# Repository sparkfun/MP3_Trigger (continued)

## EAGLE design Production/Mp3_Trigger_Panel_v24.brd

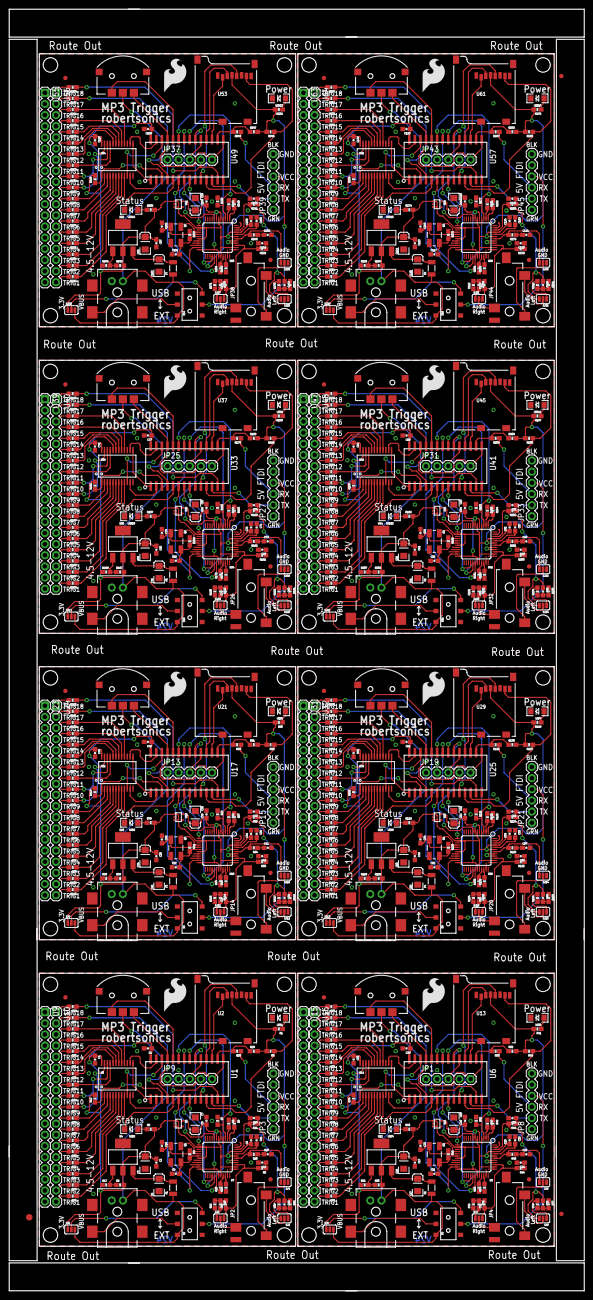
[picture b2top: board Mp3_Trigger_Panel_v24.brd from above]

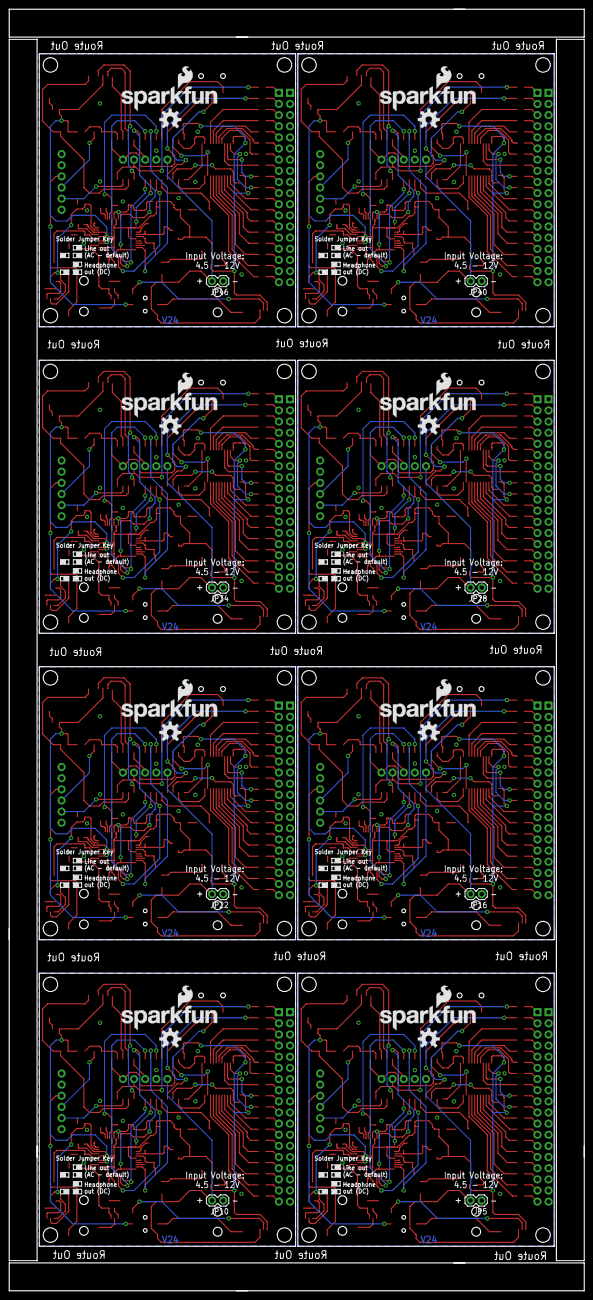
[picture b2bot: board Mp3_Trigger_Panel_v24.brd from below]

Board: 2 copper layers, 131.1 x 292.1 mm, 699 parts (24 on the bottom side), 728 nets.

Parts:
C1, C2, C4, C6, C8, C11, C17, C20, C23, C28, C29, C30, C33, C36, C39, C44, C45, C46, C49, C52, C55, C60, C61, C62, C65, C68, C71, C76, C77, C78, C81, C84, C87, C92, C93, C94, C97, C100, C103, C108, C109, C110, C113, C116, C119, C124, C125, C126: 0.1uF; 0603-CAP
C3, C5, C7, C18, C19, C27, C34, C35, C43, C50, C51, C59, C66, C67, C75, C82, C83, C91, C98, C99, C107, C114, C115, C123: 10uF; EIA3216
C9, C10, C21, C22, C37, C38, C53, C54, C69, C70, C85, C86, C101, C102, C117, C118: 22pF; 0603-CAP
C12, C14, C24, C26, C40, C42, C56, C58, C72, C74, C88, C90, C104, C106, C120, C122: 10nF; 0603-CAP
C13, C25, C41, C57, C73, C89, C105, C121: 47nF; 0603-CAP
C15, C16, C31, C32, C47, C48, C63, C64, C79, C80, C95, C96, C111, C112, C127, C128: 10uF; 0603-CAP
E$1: FIDUCIAL-1.5X3
E$5, E$6: FIDUCIAL-1X2
F1, F2, F3, F4, F5, F6, F7, F8: PTC; PTC-1206
J1, J2, J3, J4, J5, J6, J7, J8: POWER_JACKTOE; POWER_JACK_SMD_OVERPASTE_TOE
JP1, JP9, JP13, JP19, JP25, JP31, JP37, JP43: ISSP; 1X05
JP2, JP4, JP14, JP20, JP26, JP32, JP38, JP44: AUDIO-JACK; AUDIO-JACK-3.5MM-SMD
JP3, JP8, JP15, JP21, JP27, JP33, JP39, JP45: FTDI Basic; 1X06
JP5, JP10, JP16, JP22, JP28, JP34, JP40, JP46: TestPoints; 1X02
JP6, JP7, JP11, JP12, JP17, JP18, JP23, JP24, JP29, JP30, JP35, JP36, JP41, JP42, JP47, JP48: FIDUCIAL1X2; FIDUCIAL-1X2
LED1, LED3, LED5, LED7, LED9, LED11, LED13, LED15: RED; LED-1206
LED2, LED4, LED6, LED8, LED10, LED12, LED14, LED16: GREEN; LED-1206
LOGO1, LOGO2, LOGO5, LOGO7, LOGO9, LOGO11, LOGO13, LOGO15: SFE_LOGO_FLAME.3_INCH; SFE_LOGO_FLAME_.3
LOGO3, LOGO4, LOGO6, LOGO8, LOGO10, LOGO12, LOGO14, LOGO16: OSHW-LOGOM; OSHW-LOGO-M
Q1, Q2, Q3, Q4, Q5, Q6, Q7, Q8: 12.288MHz; CRYSTAL-SMD-5X3
R1, R12, R41, R74, R80, R113, R119, R152, R158, R191, R197, R230, R236, R269, R275, R308: 1K; 0603-RES
R2, R40, R79, R118, R157, R196, R235, R274: 330; 0603-RES
R3, R42, R81, R120, R159, R198, R237, R276: 1M; 0603-RES
R4, R7, R8, R14, R15, R43, R47, R48, R54, R55, R82, R86, R87, R93, R94, R121, R125, R126, R132, R133, R160, R164, R165, R171, R172, R199, R203, R204, R210, R211, R238, R242, R243, R249, R250, R277, R281, R282, R288, R289: 100k; 0603-RES
R5, R49, R88, R127, R166, R205, R244, R283: 47K; 0603-RES
R6, R50, R89, R128, R167, R206, R245, R284: 240; 0603-RES
R9, R10, R11, R44, R45, R46, R83, R84, R85, R122, R123, R124, R161, R162, R163, R200, R201, R202, R239, R240, R241, R278, R279, R280: 20; 0603-RES
R13, R39, R75, R78, R114, R117, R153, R156, R192, R195, R231, R234, R270, R273, R309, R312: 100/.25W; 0603-RES
R16, R18, R19, R52, R76, R77, R91, R115, R116, R130, R154, R155, R169, R193, R194, R208, R232, R233, R247, R271, R272, R286, R310, R311: 10K; 0603-RES
R17, R51, R90, R129, R168, R207, R246, R285: 390; 0603-RES
R20, R21, R22, R23, R24, R25, R26, R27, R28, R29, R30, R31, R32, R33, R34, R35, R36, R37, R38, R53, R56, R57, R58, R59, R60, R61, R62, R63, R64, R65, R66, R67, R68, R69, R70, R71, R72, R73, R92, R95, R96, R97, R98, R99, R100, R101, R102, R103, R104, R105, R106, R107, R108, R109, R110, R111, R112, R131, R134, R135, R136, R137, R138, R139, R140, R141, R142, R143, R144, R145, R146, R147, R148, R149, R150, R151, R170, R173, R174, R175, R176, R177, R178, R179, R180, R181, R182, R183, R184, R185, R186, R187, R188, R189, R190, R209, R212, R213, R214, R215, R216, R217, R218, R219, R220, R221, R222, R223, R224, R225, R226, R227, R228, R229, R248, R251, R252, R253, R254, R255, R256, R257, R258, R259, R260, R261, R262, R263, R264, R265, R266, R267, R268, R287, R290, R291, R292, R293, R294, R295, R296, R297, R298, R299, R300, R301, R302, R303, R304, R305, R306, R307: 100; 0603-RES
S1, S3, S5, S7, S9, S11, S13, S15: NAV_SWITCHSMD; NAV_SWITCH
S2, S4, S6, S8, S10, S12, S14, S16: DPDT; AYZ0202
SJ1, SJ5, SJ9, SJ13, SJ17, SJ21, SJ25, SJ29: UART Power; PAD-JUMPER-3-2OF3_NC_BY_PASTE_YES_SILK_FULL_BOX
SJ2, SJ8, SJ12, SJ16, SJ20, SJ24, SJ28, SJ32: AudioLeft; PAD-HUMPER-3-1&2_NC_BY_PASTE_YES_SILK_FULL_BOX
SJ3, SJ7, SJ11, SJ15, SJ19, SJ23, SJ27, SJ31: AudioRight; PAD-HUMPER-3-1&2_NC_BY_PASTE_YES_SILK_FULL_BOX
SJ4, SJ6, SJ10, SJ14, SJ18, SJ22, SJ26, SJ30: AudioGND; PAD-HUMPER-3-1&2_NC_BY_PASTE_YES_SILK_FULL_BOX
U1, U6, U17, U25, U33, U41, U49, U57: CY8C29466; SOIC-28
U2, U13, U21, U29, U37, U45, U53, U61: USD-SOCKET; MICROSD_1:1
U3, U14, U22, U30, U38, U46, U54, U62: MUX-74HC4067SMD; SSOP24
U4, U12, U20, U28, U36, U44, U52, U60: LM1117; SOT223
U5, U11, U19, U27, U35, U43, U51, U59: 1.8V Reg; SC70
U7, U8, U18, U26, U34, U42, U50, U58: VS1063; LQFP-48
U9, U10, U15, U16, U23, U24, U31, U32, U39, U40, U47, U48, U55, U56, U63, U64: M18_; 1X18
U$1, U$2, U$7, U$16, U$21, U$26, U$31, U$36: SFE_LOGO_NAME_FLAME.2_INCH; SFE_LOGO_NAME_FLAME_.2
U$3, U$4, U$5, U$6, U$8, U$9, U$10, U$11, U$12, U$13, U$14, U$15, U$17, U$18, U$19, U$20, U$22, U$23, U$24, U$25, U$27, U$28, U$29, U$30, U$32, U$33, U$34, U$35, U$37, U$38, U$39, U$40: STAND-OFF

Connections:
3.3V: C1.1, C2.1, C3.A, C4.1, C6.1, R1.2, R2.2, R5.2, R6.2, R12.2, R19.2, SJ1.1, U1.28, U2.4, U3.24, U4.2, U5.1, U5.3, U7.6, U7.14, U7.19, U7.32, U7.38, U7.43, U7.45
3.3V1: C17.1, C18.A, C28.1, C29.1, C30.1, R40.2, R41.2, R49.2, R50.2, R52.2, R74.2, SJ5.1, U6.28, U8.6, U8.14, U8.19, U8.32, U8.38, U8.43, U8.45, U11.1, U11.3, U12.2, U13.4, U14.24
3.3V2: C33.1, C34.A, C44.1, C45.1, C46.1, R79.2, R80.2, R88.2, R89.2, R91.2, R113.2, SJ9.1, U17.28, U18.6, U18.14, U18.19, U18.32, U18.38, U18.43, U18.45, U19.1, U19.3, U20.2, U21.4, U22.24
3.3V3: C49.1, C50.A, C60.1, C61.1, C62.1, R118.2, R119.2, R127.2, R128.2, R130.2, R152.2, SJ13.1, U25.28, U26.6, U26.14, U26.19, U26.32, U26.38, U26.43, U26.45, U27.1, U27.3, U28.2, U29.4, U30.24
3.3V4: C65.1, C66.A, C76.1, C77.1, C78.1, R157.2, R158.2, R166.2, R167.2, R169.2, R191.2, SJ17.1, U33.28, U34.6, U34.14, U34.19, U34.32, U34.38, U34.43, U34.45, U35.1, U35.3, U36.2, U37.4, U38.24
3.3V5: C81.1, C82.A, C92.1, C93.1, C94.1, R196.2, R197.2, R205.2, R206.2, R208.2, R230.2, SJ21.1, U41.28, U42.6, U42.14, U42.19, U42.32, U42.38, U42.43, U42.45, U43.1, U43.3, U44.2, U45.4, U46.24
3.3V6: C97.1, C98.A, C108.1, C109.1, C110.1, R235.2, R236.2, R244.2, R245.2, R247.2, R269.2, SJ25.1, U49.28, U50.6, U50.14, U50.19, U50.32, U50.38, U50.43, U50.45, U51.1, U51.3, U52.2, U53.4, U54.24
3.3V7: C113.1, C114.A, C124.1, C125.1, C126.1, R274.2, R275.2, R283.2, R284.2, R286.2, R308.2, SJ29.1, U57.28, U58.6, U58.14, U58.19, U58.32, U58.38, U58.43, U58.45, U59.1, U59.3, U60.2, U61.4, U62.24
COM: R12.1, U1.3, U3.1
COM1: R74.1, U6.3, U14.1
COM2: R113.1, U17.3, U22.1
COM3: R152.1, U25.3, U30.1
COM4: R191.1, U33.3, U38.1
COM5: R230.1, U41.3, U46.1
COM6: R269.1, U49.3, U54.1
COM7: R308.1, U57.3, U62.1
CVDD: C7.A, C8.1, U5.5, U7.5, U7.7, U7.24, U7.31
CVDD1: C19.A, C20.1, U8.5, U8.7, U8.24, U8.31, U11.5
CVDD2: C35.A, C36.1, U18.5, U18.7, U18.24, U18.31, U19.5
CVDD3: C51.A, C52.1, U26.5, U26.7, U26.24, U26.31, U27.5
CVDD4: C67.A, C68.1, U34.5, U34.7, U34.24, U34.31, U35.5
CVDD5: C83.A, C84.1, U42.5, U42.7, U42.24, U42.31, U43.5
CVDD6: C99.A, C100.1, U50.5, U50.7, U50.24, U50.31, U51.5
CVDD7: C115.A, C116.1, U58.5, U58.7, U58.24, U58.31, U59.5
FCS: U1.17, U2.2
FCS1: U6.17, U13.2
FCS2: U17.17, U21.2
FCS3: U25.17, U29.2
FCS4: U33.17, U37.2
FCS5: U41.17, U45.2
FCS6: U49.17, U53.2
FCS7: U57.17, U61.2
FDI: U1.18, U2.3
FDI1: U6.18, U13.3
FDI2: U17.18, U21.3
FDI3: U25.18, U29.3
FDI4: U33.18, U37.3
FDI5: U41.18, U45.3
FDI6: U49.18, U53.3
FDI7: U57.18, U61.3
FDO: R5.1, U1.11, U2.7
FDO1: R49.1, U6.11, U13.7
FDO2: R88.1, U17.11, U21.7
FDO3: R127.1, U25.11, U29.7
FDO4: R166.1, U33.11, U37.7
FDO5: R205.1, U41.11, U45.7
FDO6: R244.1, U49.11, U53.7
FDO7: R283.1, U57.11, U61.7
FSCK: U1.10, U2.5
FSCK1: U6.10, U13.5
FSCK2: U17.10, U21.5
FSCK3: U25.10, U29.5
FSCK4: U33.10, U37.5
FSCK5: U41.10, U45.5
FSCK6: U49.10, U53.5
FSCK7: U57.10, U61.5
GBUF: R10.2, SJ4.3, U7.42
GBUF1: R45.2, SJ6.3, U8.42
GBUF2: R84.2, SJ10.3, U18.42
GBUF3: R123.2, SJ14.3, U26.42
GBUF4: R162.2, SJ18.3, U34.42
GBUF5: R201.2, SJ22.3, U42.42
GBUF6: R240.2, SJ26.3, U50.42
GBUF7: R279.2, SJ30.3, U58.42
GND: C1.2, C2.2, C3.C, C4.2, C5.C, C6.2, C7.C, C8.2, C9.1, C10.1, C11.1, C12.2, C13.2, C14.2, J1.GND, J1.P$4, JP3.6, JP5.1, JP9.2, LED1.C, R4.1, R7.1, R8.1, R14.1, R15.1, R16.1, R17.1, R18.1, S1.C, SJ4.1, U1.14, U2.6, U2.CD1, U2.CD2, U2.GND1, U2.GND3, U3.12, U3.15, U5.2, U7.4, U7.16, U7.20, U7.21, U7.22, U7.35, U7.37, U7.40, U7.41, U7.47, U9.1, U9.2, U9.3, U9.4, U9.5, U9.6, U9.7, U9.8, U9.9, U9.10, U9.11, U9.12, U9.13, U9.14, U9.15, U9.16, U9.17, U9.18
GND1: C17.2, C18.C, C19.C, C20.2, C21.1, C22.1, C23.1, C24.2, C25.2, C26.2, C27.C, C28.2, C29.2, C30.2, J2.GND, J2.P$4, JP1.2, JP8.6, JP10.1, LED3.C, R43.1, R47.1, R48.1, R51.1, R54.1, R55.1, R76.1, R77.1, S3.C, SJ6.1, U6.14, U8.4, U8.16, U8.20, U8.21, U8.22, U8.35, U8.37, U8.40, U8.41, U8.47, U11.2, U13.6, U13.CD1, U13.CD2, U13.GND1, U13.GND3, U14.12, U14.15, U15.1, U15.2, U15.3, U15.4, U15.5, U15.6, U15.7, U15.8, U15.9, U15.10, U15.11, U15.12, U15.13, U15.14, U15.15, U15.16, U15.17, U15.18
GND2: C33.2, C34.C, C35.C, C36.2, C37.1, C38.1, C39.1, C40.2, C41.2, C42.2, C43.C, C44.2, C45.2, C46.2, J3.GND, J3.P$4, JP13.2, JP15.6, JP16.1, LED5.C, R82.1, R86.1, R87.1, R90.1, R93.1, R94.1, R115.1, R116.1, S5.C, SJ10.1, U17.14, U18.4, U18.16, U18.20, U18.21, U18.22, U18.35, U18.37, U18.40, U18.41, U18.47, U19.2, U21.6, U21.CD1, U21.CD2, U21.GND1, U21.GND3, U22.12, U22.15, U23.1, U23.2, U23.3, U23.4, U23.5, U23.6, U23.7, U23.8, U23.9, U23.10, U23.11, U23.12, U23.13, U23.14, U23.15, U23.16, U23.17, U23.18
GND3: C49.2, C50.C, C51.C, C52.2, C53.1, C54.1, C55.1, C56.2, C57.2, C58.2, C59.C, C60.2, C61.2, C62.2, J4.GND, J4.P$4, JP19.2, JP21.6, JP22.1, LED7.C, R121.1, R125.1, R126.1, R129.1, R132.1, R133.1, R154.1, R155.1, S7.C, SJ14.1, U25.14, U26.4, U26.16, U26.20, U26.21, U26.22, U26.35, U26.37, U26.40, U26.41, U26.47, U27.2, U29.6, U29.CD1, U29.CD2, U29.GND1, U29.GND3, U30.12, U30.15, U31.1, U31.2, U31.3, U31.4, U31.5, U31.6, U31.7, U31.8, U31.9, U31.10, U31.11, U31.12, U31.13, U31.14, U31.15, U31.16, U31.17, U31.18
GND4: C65.2, C66.C, C67.C, C68.2, C69.1, C70.1, C71.1, C72.2, C73.2, C74.2, C75.C, C76.2, C77.2, C78.2, J5.GND, J5.P$4, JP25.2, JP27.6, JP28.1, LED9.C, R160.1, R164.1, R165.1, R168.1, R171.1, R172.1, R193.1, R194.1, S9.C, SJ18.1, U33.14, U34.4, U34.16, U34.20, U34.21, U34.22, U34.35, U34.37, U34.40, U34.41, U34.47, U35.2, U37.6, U37.CD1, U37.CD2, U37.GND1, U37.GND3, U38.12, U38.15, U39.1, U39.2, U39.3, U39.4, U39.5, U39.6, U39.7, U39.8, U39.9, U39.10, U39.11, U39.12, U39.13, U39.14, U39.15, U39.16, U39.17, U39.18
GND5: C81.2, C82.C, C83.C, C84.2, C85.1, C86.1, C87.1, C88.2, C89.2, C90.2, C91.C, C92.2, C93.2, C94.2, J6.GND, J6.P$4, JP31.2, JP33.6, JP34.1, LED11.C, R199.1, R203.1, R204.1, R207.1, R210.1, R211.1, R232.1, R233.1, S11.C, SJ22.1, U41.14, U42.4, U42.16, U42.20, U42.21, U42.22, U42.35, U42.37, U42.40, U42.41, U42.47, U43.2, U45.6, U45.CD1, U45.CD2, U45.GND1, U45.GND3, U46.12, U46.15, U47.1, U47.2, U47.3, U47.4, U47.5, U47.6, U47.7, U47.8, U47.9, U47.10, U47.11, U47.12, U47.13, U47.14, U47.15, U47.16, U47.17, U47.18
GND6: C97.2, C98.C, C99.C, C100.2, C101.1, C102.1, C103.1, C104.2, C105.2, C106.2, C107.C, C108.2, C109.2, C110.2, J7.GND, J7.P$4, JP37.2, JP39.6, JP40.1, LED13.C, R238.1, R242.1, R243.1, R246.1, R249.1, R250.1, R271.1, R272.1, S13.C, SJ26.1, U49.14, U50.4, U50.16, U50.20, U50.21, U50.22, U50.35, U50.37, U50.40, U50.41, U50.47, U51.2, U53.6, U53.CD1, U53.CD2, U53.GND1, U53.GND3, U54.12, U54.15, U55.1, U55.2, U55.3, U55.4, U55.5, U55.6, U55.7, U55.8, U55.9, U55.10, U55.11, U55.12, U55.13, U55.14, U55.15, U55.16, U55.17, U55.18
GND7: C113.2, C114.C, C115.C, C116.2, C117.1, C118.1, C119.1, C120.2, C121.2, C122.2, C123.C, C124.2, C125.2, C126.2, J8.GND, J8.P$4, JP43.2, JP45.6, JP46.1, LED15.C, R277.1, R281.1, R282.1, R285.1, R288.1, R289.1, R310.1, R311.1, S15.C, SJ30.1, U57.14, U58.4, U58.16, U58.20, U58.21, U58.22, U58.35, U58.37, U58.40, U58.41, U58.47, U59.2, U61.6, U61.CD1, U61.CD2, U61.GND1, U61.GND3, U62.12, U62.15, U63.1, U63.2, U63.3, U63.4, U63.5, U63.6, U63.7, U63.8, U63.9, U63.10, U63.11, U63.12, U63.13, U63.14, U63.15, U63.16, U63.17, U63.18
LEFT: C16.1, R11.2, SJ2.3, U7.46
LEFT1: C32.1, R46.2, SJ8.3, U8.46
LEFT2: C48.1, R85.2, SJ12.3, U18.46
LEFT3: C64.1, R124.2, SJ16.3, U26.46
LEFT4: C80.1, R163.2, SJ20.3, U34.46
LEFT5: C96.1, R202.2, SJ24.3, U42.46
LEFT6: C112.1, R241.2, SJ28.3, U50.46
LEFT7: C128.1, R280.2, SJ32.3, U58.46
MCS: U1.22, U7.23
MCS1: U6.22, U8.23
MCS2: U17.22, U18.23
MCS3: U25.22, U26.23
MCS4: U33.22, U34.23
MCS5: U41.22, U42.23
MCS6: U49.22, U50.23
MCS7: U57.22, U58.23
MDCS: U1.7, U7.13
MDCS1: U6.7, U8.13
MDCS2: U17.7, U18.13
MDCS3: U25.7, U26.13
MDCS4: U33.7, U34.13
MDCS5: U41.7, U42.13
MDCS6: U49.7, U50.13
MDCS7: U57.7, U58.13
MDREQ: U1.20, U7.8
MDREQ1: U6.20, U8.8
MDREQ2: U17.20, U18.8
MDREQ3: U25.20, U26.8
MDREQ4: U33.20, U34.8
MDREQ5: U41.20, U42.8
MDREQ6: U49.20, U50.8
MDREQ7: U57.20, U58.8
MICN: R4.2, U7.2
MICN1: R47.2, U8.2
MICN2: R86.2, U18.2
MICN3: R125.2, U26.2
MICN4: R164.2, U34.2
MICN5: R203.2, U42.2
MICN6: R242.2, U50.2
MICN7: R281.2, U58.2
MICP: R8.2, U7.1
MICP1: R48.2, U8.1
MICP2: R87.2, U18.1
MICP3: R126.2, U26.1
MICP4: R165.2, U34.1
MICP5: R204.2, U42.1
MICP6: R243.2, U50.1
MICP7: R282.2, U58.1
MRST: R7.2, U1.23, U7.3
MRST1: R43.2, U6.23, U8.3
MRST2: R82.2, U17.23, U18.3
MRST3: R121.2, U25.23, U26.3
MRST4: R160.2, U33.23, U34.3
MRST5: R199.2, U41.23, U42.3
MRST6: R238.2, U49.23, U50.3
MRST7: R277.2, U57.23, U58.3
MSCLK: U1.8, U7.28
MSCLK1: U6.8, U8.28
MSCLK2: U17.8, U18.28
MSCLK3: U25.8, U26.28
MSCLK4: U33.8, U34.28
MSCLK5: U41.8, U42.28
MSCLK6: U49.8, U50.28
MSCLK7: U57.8, U58.28
MSI: U1.21, U7.29
MSI1: U6.21, U8.29
MSI2: U17.21, U18.29
MSI3: U25.21, U26.29
MSI4: U33.21, U34.29
MSI5: U41.21, U42.29
MSI6: U49.21, U50.29
MSI7: U57.21, U58.29
MSO: U1.6, U7.30
MSO1: U6.6, U8.30
MSO2: U17.6, U18.30
MSO3: U25.6, U26.30
MSO4: U33.6, U34.30
MSO5: U41.6, U42.30
MSO6: U49.6, U50.30
MSO7: U57.6, U58.30
unnamed: JP2.SLEEVE, SJ4.2
unnamed: R6.1, R17.2, U4.1
unnamed: C9.2, Q1.3, R3.2, U7.18
unnamed: LED1.A, R1.1
unnamed: C10.2, Q1.1, R3.1, U7.17
unnamed: JP2.RING, SJ3.2
unnamed: R13.2, SJ3.1
unnamed: C15.2, R13.1, R16.2
unnamed: LED2.A, R2.1
unnamed: R14.2, U7.34
unnamed: C11.2, U7.44
unnamed: LED2.C, U1.5
unnamed: J1.VIN0, S2.2
unnamed: C14.1, R11.1
unnamed: C13.1, R10.1
unnamed: C12.1, R9.1
unnamed: R15.2, U7.33
unnamed: C5.A, F1.2, U4.3
unnamed: JP2.TIP, SJ2.2
unnamed: S2.6, SJ1.2
unnamed: LED3.A, R41.1
unnamed: R39.2, SJ2.1
unnamed: C16.2, R18.2, R39.1
unnamed: J2.VIN0, S4.2
unnamed: C21.2, Q2.3, R42.2, U8.18
unnamed: C22.2, Q2.1, R42.1, U8.17
unnamed: C23.2, U8.44
unnamed: C26.1, R46.1
unnamed: C25.1, R45.1
unnamed: C24.1, R44.1
unnamed: LED4.A, R40.1
unnamed: R50.1, R51.2, U12.1
unnamed: LED4.C, U6.5
unnamed: S4.6, SJ5.2
unnamed: R54.2, U8.34
unnamed: R55.2, U8.33
unnamed: C27.A, F2.2, U12.3
unnamed: JP4.SLEEVE, SJ6.2
unnamed: JP4.RING, SJ7.2
unnamed: R75.2, SJ7.1
unnamed: C31.2, R75.1, R76.2
unnamed: JP4.TIP, SJ8.2
unnamed: R78.2, SJ8.1
unnamed: C32.2, R77.2, R78.1
unnamed: LED5.A, R80.1
unnamed: J3.VIN0, S6.2
unnamed: C37.2, Q3.3, R81.2, U18.18
unnamed: C38.2, Q3.1, R81.1, U18.17
unnamed: C39.2, U18.44
unnamed: C42.1, R85.1
unnamed: C41.1, R84.1
unnamed: C40.1, R83.1
unnamed: LED6.A, R79.1
unnamed: R89.1, R90.2, U20.1
unnamed: LED6.C, U17.5
unnamed: S6.6, SJ9.2
unnamed: R93.2, U18.34
unnamed: R94.2, U18.33
unnamed: C43.A, F3.2, U20.3
unnamed: JP14.SLEEVE, SJ10.2
unnamed: JP14.RING, SJ11.2
unnamed: R114.2, SJ11.1
unnamed: C47.2, R114.1, R115.2
unnamed: JP14.TIP, SJ12.2
unnamed: R117.2, SJ12.1
unnamed: C48.2, R116.2, R117.1
unnamed: LED7.A, R119.1
unnamed: J4.VIN0, S8.2
unnamed: C53.2, Q4.3, R120.2, U26.18
unnamed: C54.2, Q4.1, R120.1, U26.17
unnamed: C55.2, U26.44
unnamed: C58.1, R124.1
unnamed: C57.1, R123.1
unnamed: C56.1, R122.1
unnamed: LED8.A, R118.1
unnamed: R128.1, R129.2, U28.1
unnamed: LED8.C, U25.5
unnamed: S8.6, SJ13.2
unnamed: R132.2, U26.34
unnamed: R133.2, U26.33
unnamed: C59.A, F4.2, U28.3
unnamed: JP20.SLEEVE, SJ14.2
unnamed: JP20.RING, SJ15.2
unnamed: R153.2, SJ15.1
unnamed: C63.2, R153.1, R154.2
unnamed: JP20.TIP, SJ16.2
unnamed: R156.2, SJ16.1
unnamed: C64.2, R155.2, R156.1
unnamed: LED9.A, R158.1
unnamed: J5.VIN0, S10.2
unnamed: C69.2, Q5.3, R159.2, U34.18
unnamed: C70.2, Q5.1, R159.1, U34.17
unnamed: C71.2, U34.44
unnamed: C74.1, R163.1
unnamed: C73.1, R162.1
unnamed: C72.1, R161.1
unnamed: LED10.A, R157.1
unnamed: R167.1, R168.2, U36.1
unnamed: LED10.C, U33.5
unnamed: S10.6, SJ17.2
unnamed: R171.2, U34.34
unnamed: R172.2, U34.33
unnamed: C75.A, F5.2, U36.3
unnamed: JP26.SLEEVE, SJ18.2
unnamed: JP26.RING, SJ19.2
unnamed: R192.2, SJ19.1
unnamed: C79.2, R192.1, R193.2
unnamed: JP26.TIP, SJ20.2
unnamed: R195.2, SJ20.1
unnamed: C80.2, R194.2, R195.1
unnamed: LED11.A, R197.1
unnamed: J6.VIN0, S12.2
unnamed: C85.2, Q6.3, R198.2, U42.18
unnamed: C86.2, Q6.1, R198.1, U42.17
unnamed: C87.2, U42.44
unnamed: C90.1, R202.1
unnamed: C89.1, R201.1
unnamed: C88.1, R200.1
unnamed: LED12.A, R196.1
unnamed: R206.1, R207.2, U44.1
unnamed: LED12.C, U41.5
unnamed: S12.6, SJ21.2
unnamed: R210.2, U42.34
unnamed: R211.2, U42.33
unnamed: C91.A, F6.2, U44.3
unnamed: JP32.SLEEVE, SJ22.2
unnamed: JP32.RING, SJ23.2
unnamed: R231.2, SJ23.1
unnamed: C95.2, R231.1, R232.2
unnamed: JP32.TIP, SJ24.2
unnamed: R234.2, SJ24.1
unnamed: C96.2, R233.2, R234.1
unnamed: LED13.A, R236.1
unnamed: J7.VIN0, S14.2
unnamed: C101.2, Q7.3, R237.2, U50.18
unnamed: C102.2, Q7.1, R237.1, U50.17
unnamed: C103.2, U50.44
unnamed: C106.1, R241.1
unnamed: C105.1, R240.1
unnamed: C104.1, R239.1
unnamed: LED14.A, R235.1
unnamed: R245.1, R246.2, U52.1
unnamed: LED14.C, U49.5
unnamed: S14.6, SJ25.2
unnamed: R249.2, U50.34
unnamed: R250.2, U50.33
unnamed: C107.A, F7.2, U52.3
unnamed: JP38.SLEEVE, SJ26.2
unnamed: JP38.RING, SJ27.2
unnamed: R270.2, SJ27.1
unnamed: C111.2, R270.1, R271.2
unnamed: JP38.TIP, SJ28.2
unnamed: R273.2, SJ28.1
unnamed: C112.2, R272.2, R273.1
unnamed: LED15.A, R275.1
unnamed: J8.VIN0, S16.2
unnamed: C117.2, Q8.3, R276.2, U58.18
unnamed: C118.2, Q8.1, R276.1, U58.17
unnamed: C119.2, U58.44
unnamed: C122.1, R280.1
unnamed: C121.1, R279.1
unnamed: C120.1, R278.1
unnamed: LED16.A, R274.1
unnamed: R284.1, R285.2, U60.1
unnamed: LED16.C, U57.5
unnamed: S16.6, SJ29.2
unnamed: R288.2, U58.34
unnamed: R289.2, U58.33
unnamed: C123.A, F8.2, U60.3
unnamed: JP44.SLEEVE, SJ30.2
unnamed: JP44.RING, SJ31.2
unnamed: R309.2, SJ31.1
unnamed: C127.2, R309.1, R310.2
unnamed: JP44.TIP, SJ32.2
unnamed: R312.2, SJ32.1
unnamed: C128.2, R311.2, R312.1
RIGHT: C15.1, R9.2, SJ3.3, U7.39
RIGHT1: C31.1, R44.2, SJ7.3, U8.39
RIGHT2: C47.1, R83.2, SJ11.3, U18.39
RIGHT3: C63.1, R122.2, SJ15.3, U26.39
RIGHT4: C79.1, R161.2, SJ19.3, U34.39
RIGHT5: C95.1, R200.2, SJ23.3, U42.39
RIGHT6: C111.1, R239.2, SJ27.3, U50.39
RIGHT7: C127.1, R278.2, SJ31.3, U58.39
RX: R19.1, R20.2, U1.16
RX1: R52.1, R53.2, U6.16
RX2: R91.1, R92.2, U17.16
RX3: R130.1, R131.2, U25.16
RX4: R169.1, R170.2, U33.16
RX5: R208.1, R209.2, U41.16
RX6: R247.1, R248.2, U49.16
RX7: R286.1, R287.2, U57.16
RX-I: JP3.3, R20.1
RX-I1: JP8.3, R53.1
RX-I2: JP15.3, R92.1
RX-I3: JP21.3, R131.1
RX-I4: JP27.3, R170.1
RX-I5: JP33.3, R209.1
RX-I6: JP39.3, R248.1
RX-I7: JP45.3, R287.1
S0: U1.26, U3.10
S1: U1.2, U3.11
S2: U1.27, U3.14
S3: U1.1, U3.13
S4: U6.26, U14.10
S5: U6.2, U14.11
S6: U6.27, U14.14
S7: U6.1, U14.13
S8: U17.26, U22.10
S9: U17.2, U22.11
S10: U17.27, U22.14
S11: U17.1, U22.13
S12: U25.26, U30.10
S13: U25.2, U30.11
S14: U25.27, U30.14
S15: U25.1, U30.13
S16: U33.26, U38.10
S17: U33.2, U38.11
S18: U33.27, U38.14
S19: U33.1, U38.13
S20: U41.26, U46.10
S21: U41.2, U46.11
S22: U41.27, U46.14
S23: U41.1, U46.13
S24: U49.26, U54.10
S25: U49.2, U54.11
S26: U49.27, U54.14
S27: U49.1, U54.13
S28: U57.26, U62.10
S29: U57.2, U62.11
S30: U57.27, U62.14
S31: U57.1, U62.13
SW1: S1.1, U1.24
SW2: S1.T, U1.4
SW3: S1.2, U1.25
SW4: S3.T, U6.4
SW5: S3.2, U6.25
SW6: S3.1, U6.24
SW7: S5.T, U17.4
SW8: S5.2, U17.25
SW9: S5.1, U17.24
SW10: S7.T, U25.4
SW11: S7.2, U25.25
SW12: S7.1, U25.24
SW13: S9.T, U33.4
SW14: S9.2, U33.25
SW15: S9.1, U33.24
SW16: S11.T, U41.4
SW17: S11.2, U41.25
SW18: S11.1, U41.24
SW19: S13.T, U49.4
SW20: S13.2, U49.25
SW21: S13.1, U49.24
SW22: S15.T, U57.4
SW23: S15.2, U57.25
SW24: S15.1, U57.24
T1: R36.2, U10.18
T2: R35.2, U10.17
T3: R21.2, U10.16
T4: R22.2, U10.15
T5: R23.2, U10.14
T6: R24.2, U10.13
T7: R25.2, U10.12
T8: R26.2, U10.11
T9: R27.2, U10.10
T10: R28.2, U10.9
T11: R29.2, U10.8
T12: R30.2, U10.7
T13: R31.2, U10.6
T14: R32.2, U10.5
T15: R33.2, U10.4
T16: R34.2, U10.3
T17: R37.2, U10.2
T18: R38.2, U10.1
T19: R71.2, U16.18
T20: R70.2, U16.17
T21: R56.2, U16.16
T22: R57.2, U16.15
T23: R58.2, U16.14
T24: R59.2, U16.13
T25: R60.2, U16.12
T26: R61.2, U16.11
T27: R62.2, U16.10
T28: R63.2, U16.9
T29: R64.2, U16.8
T30: R65.2, U16.7
T31: R66.2, U16.6
T32: R67.2, U16.5
T33: R68.2, U16.4
T34: R69.2, U16.3
T35: R72.2, U16.2
T36: R73.2, U16.1
T37: R110.2, U24.18
T38: R109.2, U24.17
T39: R95.2, U24.16
T40: R96.2, U24.15
T41: R97.2, U24.14
T42: R98.2, U24.13
T43: R99.2, U24.12
T44: R100.2, U24.11
T45: R101.2, U24.10
T46: R102.2, U24.9
T47: R103.2, U24.8
T48: R104.2, U24.7
T49: R105.2, U24.6
T50: R106.2, U24.5
T51: R107.2, U24.4
T52: R108.2, U24.3
T53: R111.2, U24.2
T54: R112.2, U24.1
T55: R149.2, U32.18
T56: R148.2, U32.17
T57: R134.2, U32.16
T58: R135.2, U32.15
T59: R136.2, U32.14
T60: R137.2, U32.13
T61: R138.2, U32.12
T62: R139.2, U32.11
T63: R140.2, U32.10
T64: R141.2, U32.9
T65: R142.2, U32.8
T66: R143.2, U32.7
T67: R144.2, U32.6
T68: R145.2, U32.5
T69: R146.2, U32.4
T70: R147.2, U32.3
T71: R150.2, U32.2
T72: R151.2, U32.1
T73: R188.2, U40.18
T74: R187.2, U40.17
T75: R173.2, U40.16
T76: R174.2, U40.15
T77: R175.2, U40.14
T78: R176.2, U40.13
T79: R177.2, U40.12
T80: R178.2, U40.11
T81: R179.2, U40.10
T82: R180.2, U40.9
T83: R181.2, U40.8
T84: R182.2, U40.7
T85: R183.2, U40.6
T86: R184.2, U40.5
T87: R185.2, U40.4
T88: R186.2, U40.3
T89: R189.2, U40.2
T90: R190.2, U40.1
T91: R227.2, U48.18
T92: R226.2, U48.17
T93: R212.2, U48.16
T94: R213.2, U48.15
T95: R214.2, U48.14
T96: R215.2, U48.13
T97: R216.2, U48.12
T98: R217.2, U48.11
T99: R218.2, U48.10
T100: R219.2, U48.9
T101: R220.2, U48.8
T102: R221.2, U48.7
T103: R222.2, U48.6
T104: R223.2, U48.5
T105: R224.2, U48.4
T106: R225.2, U48.3
T107: R228.2, U48.2
T108: R229.2, U48.1
T109: R266.2, U56.18
T110: R265.2, U56.17
T111: R251.2, U56.16
T112: R252.2, U56.15
T113: R253.2, U56.14
T114: R254.2, U56.13
T115: R255.2, U56.12
T116: R256.2, U56.11
T117: R257.2, U56.10
T118: R258.2, U56.9
T119: R259.2, U56.8
T120: R260.2, U56.7
T121: R261.2, U56.6
T122: R262.2, U56.5
T123: R263.2, U56.4
T124: R264.2, U56.3
T125: R267.2, U56.2
T126: R268.2, U56.1
T127: R305.2, U64.18
T128: R304.2, U64.17
T129: R290.2, U64.16
T130: R291.2, U64.15
T131: R292.2, U64.14
T132: R293.2, U64.13
T133: R294.2, U64.12
T134: R295.2, U64.11
T135: R296.2, U64.10
T136: R297.2, U64.9
T137: R298.2, U64.8
T138: R299.2, U64.7
T139: R300.2, U64.6
T140: R301.2, U64.5
T141: R302.2, U64.4
T142: R303.2, U64.3
T143: R306.2, U64.2
T144: R307.2, U64.1
TRIG1: R36.1, U3.9
TRIG2: R35.1, U3.8
TRIG3: R21.1, U3.7
TRIG4: R22.1, U3.6
TRIG5: R23.1, U3.5
TRIG6: R24.1, U3.4
TRIG7: R25.1, U3.3
TRIG8: R26.1, U3.2
TRIG9: R27.1, U3.23
TRIG10: R28.1, U3.22
TRIG11: R29.1, U3.21
TRIG12: R30.1, U3.20
TRIG13: R31.1, U3.19
TRIG14: R32.1, U3.18
TRIG15: R33.1, U3.17
TRIG16: R34.1, U3.16
TRIG17: JP9.5, R37.1, U1.15
TRIG18: JP9.4, R38.1, U1.13
TRIG19: JP1.5, R72.1, U6.15
TRIG20: JP1.4, R73.1, U6.13
TRIG21: R69.1, U14.16
TRIG22: R68.1, U14.17
TRIG23: R67.1, U14.18
TRIG24: R66.1, U14.19
TRIG25: R65.1, U14.20
TRIG26: R64.1, U14.21
TRIG27: R63.1, U14.22
TRIG28: R62.1, U14.23
TRIG29: R61.1, U14.2
TRIG30: R60.1, U14.3
TRIG31: R59.1, U14.4
TRIG32: R58.1, U14.5
TRIG33: R57.1, U14.6
TRIG34: R56.1, U14.7
TRIG35: R70.1, U14.8
TRIG36: R71.1, U14.9
TRIG37: JP13.5, R111.1, U17.15
TRIG38: JP13.4, R112.1, U17.13
TRIG39: R108.1, U22.16
TRIG40: R107.1, U22.17
TRIG41: R106.1, U22.18
TRIG42: R105.1, U22.19
TRIG43: R104.1, U22.20
TRIG44: R103.1, U22.21
TRIG45: R102.1, U22.22
TRIG46: R101.1, U22.23
TRIG47: R100.1, U22.2
TRIG48: R99.1, U22.3
TRIG49: R98.1, U22.4
TRIG50: R97.1, U22.5
TRIG51: R96.1, U22.6
TRIG52: R95.1, U22.7
TRIG53: R109.1, U22.8
TRIG54: R110.1, U22.9
TRIG55: JP19.5, R150.1, U25.15
TRIG56: JP19.4, R151.1, U25.13
TRIG57: R147.1, U30.16
TRIG58: R146.1, U30.17
TRIG59: R145.1, U30.18
TRIG60: R144.1, U30.19
TRIG61: R143.1, U30.20
TRIG62: R142.1, U30.21
TRIG63: R141.1, U30.22
TRIG64: R140.1, U30.23
TRIG65: R139.1, U30.2
TRIG66: R138.1, U30.3
TRIG67: R137.1, U30.4
TRIG68: R136.1, U30.5
TRIG69: R135.1, U30.6
TRIG70: R134.1, U30.7
TRIG71: R148.1, U30.8
TRIG72: R149.1, U30.9
TRIG73: JP25.5, R189.1, U33.15
TRIG74: JP25.4, R190.1, U33.13
TRIG75: R186.1, U38.16
TRIG76: R185.1, U38.17
TRIG77: R184.1, U38.18
TRIG78: R183.1, U38.19
TRIG79: R182.1, U38.20
TRIG80: R181.1, U38.21
TRIG81: R180.1, U38.22
TRIG82: R179.1, U38.23
TRIG83: R178.1, U38.2
TRIG84: R177.1, U38.3
TRIG85: R176.1, U38.4
TRIG86: R175.1, U38.5
TRIG87: R174.1, U38.6
TRIG88: R173.1, U38.7
TRIG89: R187.1, U38.8
TRIG90: R188.1, U38.9
TRIG91: JP31.5, R228.1, U41.15
TRIG92: JP31.4, R229.1, U41.13
TRIG93: R225.1, U46.16
TRIG94: R224.1, U46.17
TRIG95: R223.1, U46.18
TRIG96: R222.1, U46.19
TRIG97: R221.1, U46.20
TRIG98: R220.1, U46.21
TRIG99: R219.1, U46.22
TRIG100: R218.1, U46.23
TRIG101: R217.1, U46.2
TRIG102: R216.1, U46.3
TRIG103: R215.1, U46.4
TRIG104: R214.1, U46.5
TRIG105: R213.1, U46.6
TRIG106: R212.1, U46.7
TRIG107: R226.1, U46.8
TRIG108: R227.1, U46.9
TRIG109: JP37.5, R267.1, U49.15
TRIG110: JP37.4, R268.1, U49.13
TRIG111: R264.1, U54.16
TRIG112: R263.1, U54.17
TRIG113: R262.1, U54.18
TRIG114: R261.1, U54.19
TRIG115: R260.1, U54.20
TRIG116: R259.1, U54.21
TRIG117: R258.1, U54.22
TRIG118: R257.1, U54.23
TRIG119: R256.1, U54.2
TRIG120: R255.1, U54.3
TRIG121: R254.1, U54.4
TRIG122: R253.1, U54.5
TRIG123: R252.1, U54.6
TRIG124: R251.1, U54.7
TRIG125: R265.1, U54.8
TRIG126: R266.1, U54.9
TRIG127: JP43.5, R306.1, U57.15
TRIG128: JP43.4, R307.1, U57.13
TRIG129: R303.1, U62.16
TRIG130: R302.1, U62.17
TRIG131: R301.1, U62.18
TRIG132: R300.1, U62.19
TRIG133: R299.1, U62.20
TRIG134: R298.1, U62.21
TRIG135: R297.1, U62.22
TRIG136: R296.1, U62.23
TRIG137: R295.1, U62.2
TRIG138: R294.1, U62.3
TRIG139: R293.1, U62.4
TRIG140: R292.1, U62.5
TRIG141: R291.1, U62.6
TRIG142: R290.1, U62.7
TRIG143: R304.1, U62.8
TRIG144: R305.1, U62.9
TX: JP3.2, U1.12
TX1: JP8.2, U6.12
TX2: JP15.2, U17.12
TX3: JP21.2, U25.12
TX4: JP27.2, U33.12
TX5: JP33.2, U41.12
TX6: JP39.2, U49.12
TX7: JP45.2, U57.12
USBVCC: JP3.4, S2.5
USBVCC1: JP8.4, S4.5
USBVCC2: JP15.4, S6.5
USBVCC3: JP21.4, S8.5
USBVCC4: JP27.4, S10.5
USBVCC5: JP33.4, S12.5
USBVCC6: JP39.4, S14.5
USBVCC7: JP45.4, S16.5
VBUS: F1.1, JP5.2, JP9.1, S2.1, SJ1.3
VBUS1: F2.1, JP1.1, JP10.2, S4.1, SJ5.3
VBUS2: F3.1, JP13.1, JP16.2, S6.1, SJ9.3
VBUS3: F4.1, JP19.1, JP22.2, S8.1, SJ13.3
VBUS4: F5.1, JP25.1, JP28.2, S10.1, SJ17.3
VBUS5: F6.1, JP31.1, JP34.2, S12.1, SJ21.3
VBUS6: F7.1, JP37.1, JP40.2, S14.1, SJ25.3
VBUS7: F8.1, JP43.1, JP46.2, S16.1, SJ29.3
XRES: JP9.3, U1.19
XRES1: JP1.3, U6.19
XRES2: JP13.3, U17.19
XRES3: JP19.3, U25.19
XRES4: JP25.3, U33.19
XRES5: JP31.3, U41.19
XRES6: JP37.3, U49.19
XRES7: JP43.3, U57.19

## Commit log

2015-03-10 Adding hardware files, updating README
2015-03-10 Fixing README license
2015-03-10 Adding collaboration info to README
2015-07-09 V24 preliminary rerouting finished
    New V24 preliminary rerouting finished after adding pulp and jumpers on
    audio lines.
2015-07-13 Minor changes from Toni K review
    Acid trap elimination, angles, added notes about jumpers, minor
    rerouting.
2015-07-13 Added OSHW Logo
    Added OSHW Logo
2015-07-29 QC Checklist Crrections
    Minor error fixes
2015-09-24 Ready for reds
    Added Input Voltages to silk, bumped up cream for solder jumpers,
    centered logos on back.
2015-09-29 FTDI Silk update
    Changed to 5V FTDI
2015-09-29 Added Jumper key to Bottom Silk
    Added solder jumper key to denote which solder jumper configurations
    mean which audio output.
2015-10-01 V24 Reds Checklist Updates
    See github for issues fixed
2015-10-07 created panel v24
2015-11-04 Updated RED LED to correct version w/ correct ID
2016-02-29 Updated README
    This part has a 3D Model. 3D Model Repo link added.
2016-06-02 Adding links to readme, adding license file
